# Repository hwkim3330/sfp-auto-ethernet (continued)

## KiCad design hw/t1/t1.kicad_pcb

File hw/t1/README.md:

# T1 SFP: 100/1000BASE-T1

Schematic, PCB (4 layers, routed), fab outputs and firmware are all in place.
**Order files are in [`jlc/`](jlc/), and the order sheet is [ORDER.md](ORDER.md).** The only open choice is **which PHY to use** (TG720 stock problem).

| Top | Bottom |
|---|---|
|  |  |

## Status

| | Result | How it was checked |
|---|---|---|
| Schematic | **ERC 0 errors, 0 warnings** ([erc.rpt](erc.rpt)) | eeschema's own ERC (`run_erc.sh`) |
| Schematic ↔ netlist | 175 pins, 0 mismatches | Netlist exported with `kicad-cli sch export netlist`, compared against the netlist in `make_t1.py` |
| Placement | 65 parts, no overlaps; housing height limits met | `make_t1.py` |
| Routing | **DRC 0 violations, 0 unconnected** ([drc.rpt](drc.rpt)) | Freerouting 1.9.0, then KiCad DRC |
| KiCad 9 | **DRC 0 errors, schematic parity clean, ERC 0 errors** ([kicad9-drc.rpt](kicad9-drc.rpt), [kicad9-erc.rpt](kicad9-erc.rpt)) | `sh ../check_kicad9.sh t1`: the official KiCad 9 image, as a reviewer would open it. Only warnings are "differs from the library copy" (KiCad 9's libraries hold newer revisions of the same parts) |
| Fab | Gerbers + drill ([fab/t1-gerbers.zip](fab/t1-gerbers.zip)), [BOM](fab/t1-bom.csv), [CPL](fab/t1-cpl.csv) | `export_t1.py` |
| Firmware | Builds: 1.7 KB flash / 280 B RAM, 0 warnings ([../../fw](../../fw)) | `make` |

## Circuit (every block is from its datasheet)

- **PHY:** DP83TG720S-Q1 (1000BASE-T1).
  - The **DP83TC812S-Q1 (100BASE-T1) fits the same footprint**. For the 100 Mb loadout, leave **FB3** unfitted (the 1.0 V buck → pins 9/21 ferrite); the TC812 regulates pin 21 itself.
  - The straps are all left at their defaults: SGMII, PHY address 0, autonomous, slave. The MCU must still set the SGMII polarity bits at start-up (see below).
- **SGMII:** SFP TD/RD → 100 nF AC coupling inside the module (as the MSA requires) → PHY TX_P/M (32/33) and RX_P/M (24/23).
- **MDI (Figure 8-1 / Table 8-1):** TRD → 100 nF DC-block → DLW32MH101XT2 CMC → H-MTD. CM termination is 2 × 1 kΩ to a node, then 4.7 nF + 100 kΩ from the node to GND. ESD is optional and left unfitted.
- **Power (Figure 8-3 / Table 8-2):**
  - The host's 3.3 V enters through the MSA's ferrites and a **TPS22918 load switch** (soft start ≈3.6 ms).
  - VDDA, VDDIO and VDD1P0 each get their own ferrite island.
  - Every power pin gets 10 nF + 100 nF; some also get 2.2 µF.
  - The decaps sit on the **bottom side**, in a ring under the PHY.
  - 1.0 V comes from a **TPS62822 buck**: 470 nH, 66.5 k / 100 k divider, 120 pF Cff.
  - Estimated module power **~0.7 W**, inside the SFP's 1.0 W power-up limit.
- **MCU:** STM32G031. It answers the host's I²C as the EEPROM (0x50) and the PHY bridge (0x56), and handles MDIO, TX_DISABLE and RX_LOS. See [`../../fw/`](../../fw/).

## Board

- 64.5 × 11.8 mm (the H-MTD overhangs a further 3.5 mm). The tab is 9.2 mm wide.
- Edge connector is the INF-8074i pattern (`../fp/sfp.pretty/SFP_Module_Edge`).
- 4 layers, **F / GND / GND / B** (JLC04101H-3313, 1.0 mm):

  | Layer | Use |
  |---|---|
  | F | pairs + signals + GND pour |
  | In1 | GND (solid) |
  | In2 | GND pour; slow signals (MDIO, LEDs, straps) may cross it, **except** under the bottom-side RX pair (`IN2_KEEPOUTS`), so every pair on B has an unbroken GND under it |
  | B | pairs + signals + GND pour |

- No pour among the edge fingers. A 0.6 mm no-copper strip runs along every edge (the panel's mouse-bite holes).
- The PHY's exposed pad gets 3 × 3 thermal vias to the planes.

## Changes after the design review (2026-09-30)

- **Every pair is laid by hand, coupled**, in `make_t1.py` (`_pair`): 0.114 mm lines, 0.152 mm gap (≈100 Ω differential on 3313), both lines on one layer with the same vias. The router only does the slow nets. From [lengths.txt](lengths.txt):

  | Pair | Layers | Vias P/N | Skew |
  |---|---|---|---|
  | SG_TX (SFP TD → PHY) | F | 0/0 | 0.44 mm |
  | SG_RX (PHY → SFP RD) | F | 0/0 | 0.00 mm |
  | TRD (PHY → DC block) | F | 0/0 | 0.44 mm |
  | DCB (DC block → CMC) | F | 0/0 | 0.08 mm |
  | MDI (CMC → H-MTD) | F | 0/0 | 2.25 mm |

  0.44 mm is about 3 ps, against an 800 ps SGMII UI.
- **SGMII polarity: both lanes run straight, P to P** (since the SFP edge fix of 2026-10; before it the edge was mirrored and the firmware inverted both lanes in SGMII_CTRL_1 bits 7/8). The firmware now leaves those bits at their reset 0. **Not verified on hardware.**
- **3.3 V inrush: TPS22918 load switch (U4).** The host's filtered 3.3 V → FB1/FB2 → VIN_RAW (1 µF) → U4 → +3V3 (10 µF). CT = 2.2 nF gives a ≈3.6 ms rise, so the 10 µF and the decaps load softly and the MSA's hot-plug limit holds by design. **Measure it on the first board.**
- **Two BOMs**: `jlc/bom-tg720.csv` + `cpl-tg720.csv` (1000BASE-T1) and `jlc/bom-tc812.csv` + `cpl-tc812.csv` (100BASE-T1: U1 = C3225813, FB3 left off).
- **H-MTD 1:1 print**: [fab/t1-1to1.pdf](fab/t1-1to1.pdf) (F.Cu + outline at 100 %). Print it without scaling and set the real connector on it before ordering.
- **Gold fingers are ENIG**, not the MSA's hard gold (≥ 0.38 µm). JLC offers no hard gold. Fine for tens of insertions on a bench; for a module that gets plugged often, order from a fab that plates hard gold (e.g. PCBWay).

## Earlier changes for ordering (2026-09-29)

- **H-MTD J2 = Rosenberger E6S20A-40MT5-Z**, drawn from the layout drawing MB_633.
  - Ground holes Ø1.74 / pad 2.5, **7.0 × 7.5** apart. The research said 9.3, but that is the outer width of the hatched areas; I measured the drawing myself.
  - Signal holes Ø0.7, 2.0 apart, 1.87 behind the front row.
  - The hatched solder areas are GND pads, and the no-routing keep-outs are rule areas.
  - Overhangs the board edge by 3.5 mm. The body sits entirely outside the cage, so the board is 64.5 mm long.
  - LCSC has no stock: hand-solder it.
- **U1 pins 12/13 cross over on purpose.** They leave the package M-over-P and the CMC takes P-over-M. The DP83TG720 corrects MDI polarity itself, and that can't be disabled (datasheet 6.4.7.2), so pin 12 drives the line's M side.
- **Buck is the TPS62822** (the TPS62821 is out of stock at LCSC; same package, pins and divider).
- **Panel (`panel_t1.py`):**
  - 5 boards, mouse-bites, **rails on 3 sides only** so the gold-finger edge stays straight (`../panel_rails.py`).
  - KiKit 1.6.0 is the version that works with KiCad 7; its `fab jlcpcb` can't drive this plotter, so the gerbers, BOM and CPL are written by our own code.

## Regenerating

```bash
python3 make_t1.py            # symbols, footprints, schematic, placed PCB (with nets)
sh run_erc.sh                 # eeschema ERC -> erc.rpt (headless, Xvfb)
python3 make_t1.py --route    # + planes, Freerouting, SES in, pours, DRC -> drc.rpt
python3 make_t1.py --reuse-ses  # reuse t1.ses (Freerouting results vary from run to run)
python3 export_t1.py          # single-board gerbers, BOM, CPL, previews, 1:1 PDF -> fab/
sh ../check_kicad9.sh t1      # the same board in KiCad 9: DRC + schematic parity + ERC
python3 panel_t1.py 5         # 5-board panel + JLC order files -> jlc/ (KiKit 1.6.0)
```

- The router is **Freerouting 1.9.0**, at `~/.local/share/freerouting/freerouting-1.9.0.jar`.
  - 2.x ignores the pass limit on the command line and never finishes on this board.
  - 1.9.0 needs a display, so it gets Xvfb `:98`.
- Freerouting's result changes on every run. **`t1.ses` in this repo is the run that came out DRC-clean.**
- Where the router kept failing, the design file lays copper before it runs, all locked:
  - `PREROUTES` / `PREVIAS`, hand-drawn:
    - every high-speed pair (above);
    - EN→VIN of the buck, routed under U3 because the no-connect PG pin blocks the direct way;
    - escape vias for U1's MDC/INT/RST, which share one lane past the crystal;
    - spokes from the pin 11/21 decap row to U1's bottom EP pad;
    - a shared ground via for C10/C16 and one for R4;
    - where the 0.6 mm edge strip closed the router's way: U4's ON pin, MDC, VDD1P0 pin 21, the MCU's ground, XO.
  - A ground via beside every capacitor ("dogbone"), except where `NO_DOGBONE` says it blocks a lane: the crystal's load caps and C21.
- After routing, `sfpgen` repairs what is left, keeping each change only if DRC is no worse:
  - removes escape vias the router didn't use;
  - joins open signal links (straight, via bridge, or a T into an existing track), before stitching so those links get the space first;
  - lays the GND stitching grid, 1 mm off the long edges where the panel's mouse bites are;
  - vias into ground islands.
- The panel's mouse-bite holes sit 0.1 mm into the board (was 0.25): at 0.25 they came within 0.16 mm of an In2 trace.
- KiCad 7 quirks, recorded in the code:
  - Standalone `LoadBoard` does not read `.kicad_pro`, so the rules are set in memory (`apply_rules`).
  - A footprint must be added to the board before `Flip`, or it segfaults.
  - A pad's `SetPos0` is required, or every pad collapses to the footprint origin.

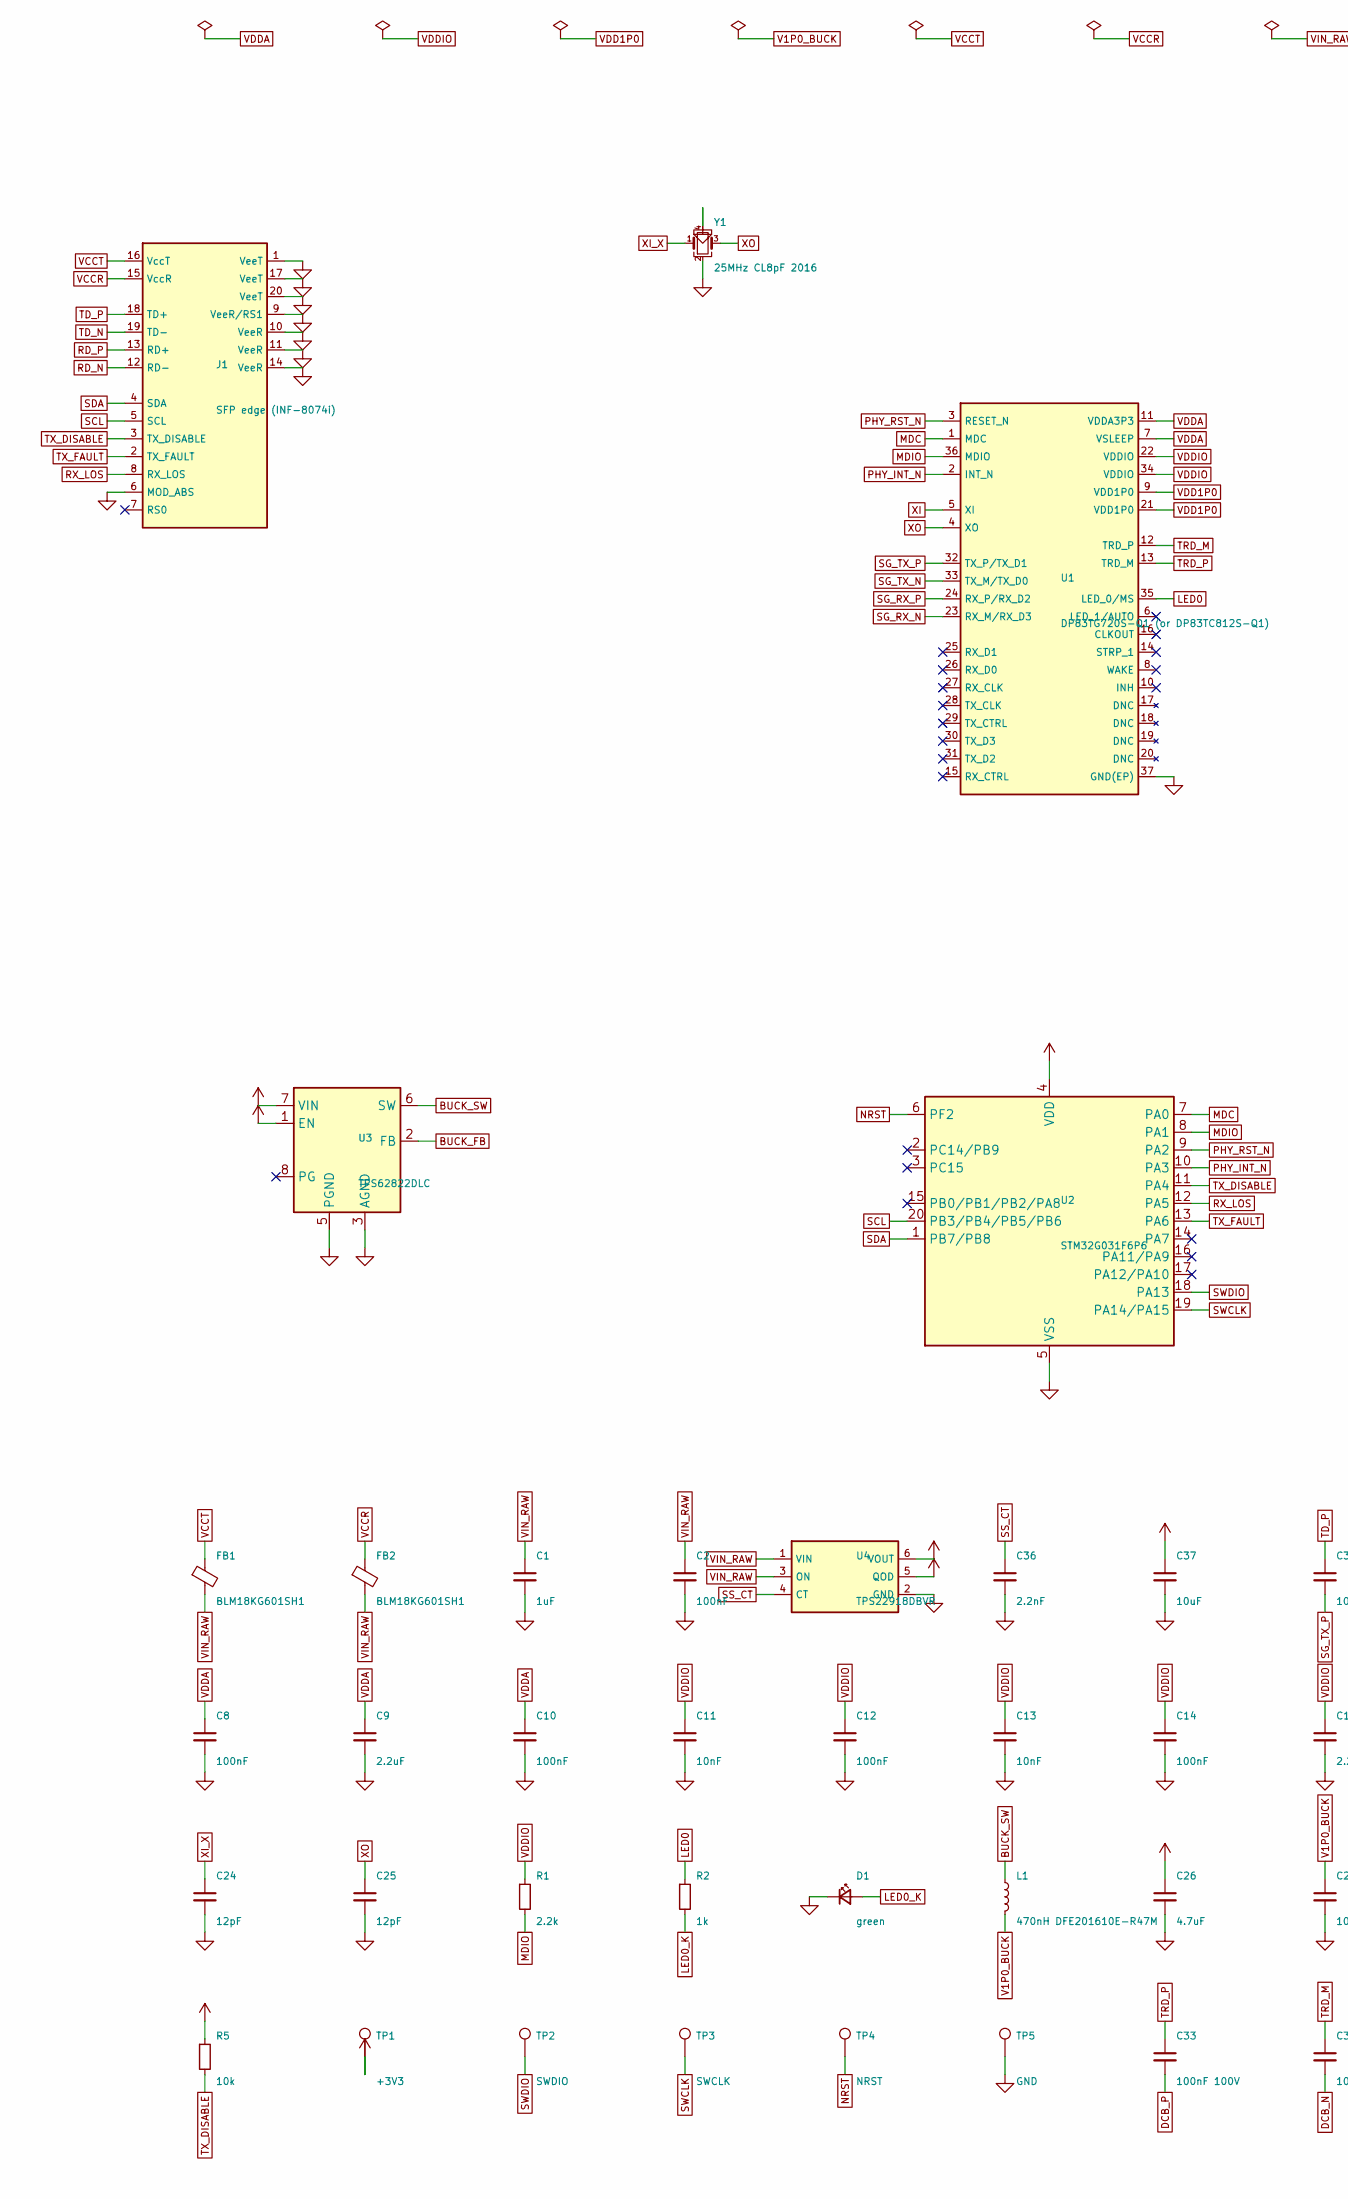
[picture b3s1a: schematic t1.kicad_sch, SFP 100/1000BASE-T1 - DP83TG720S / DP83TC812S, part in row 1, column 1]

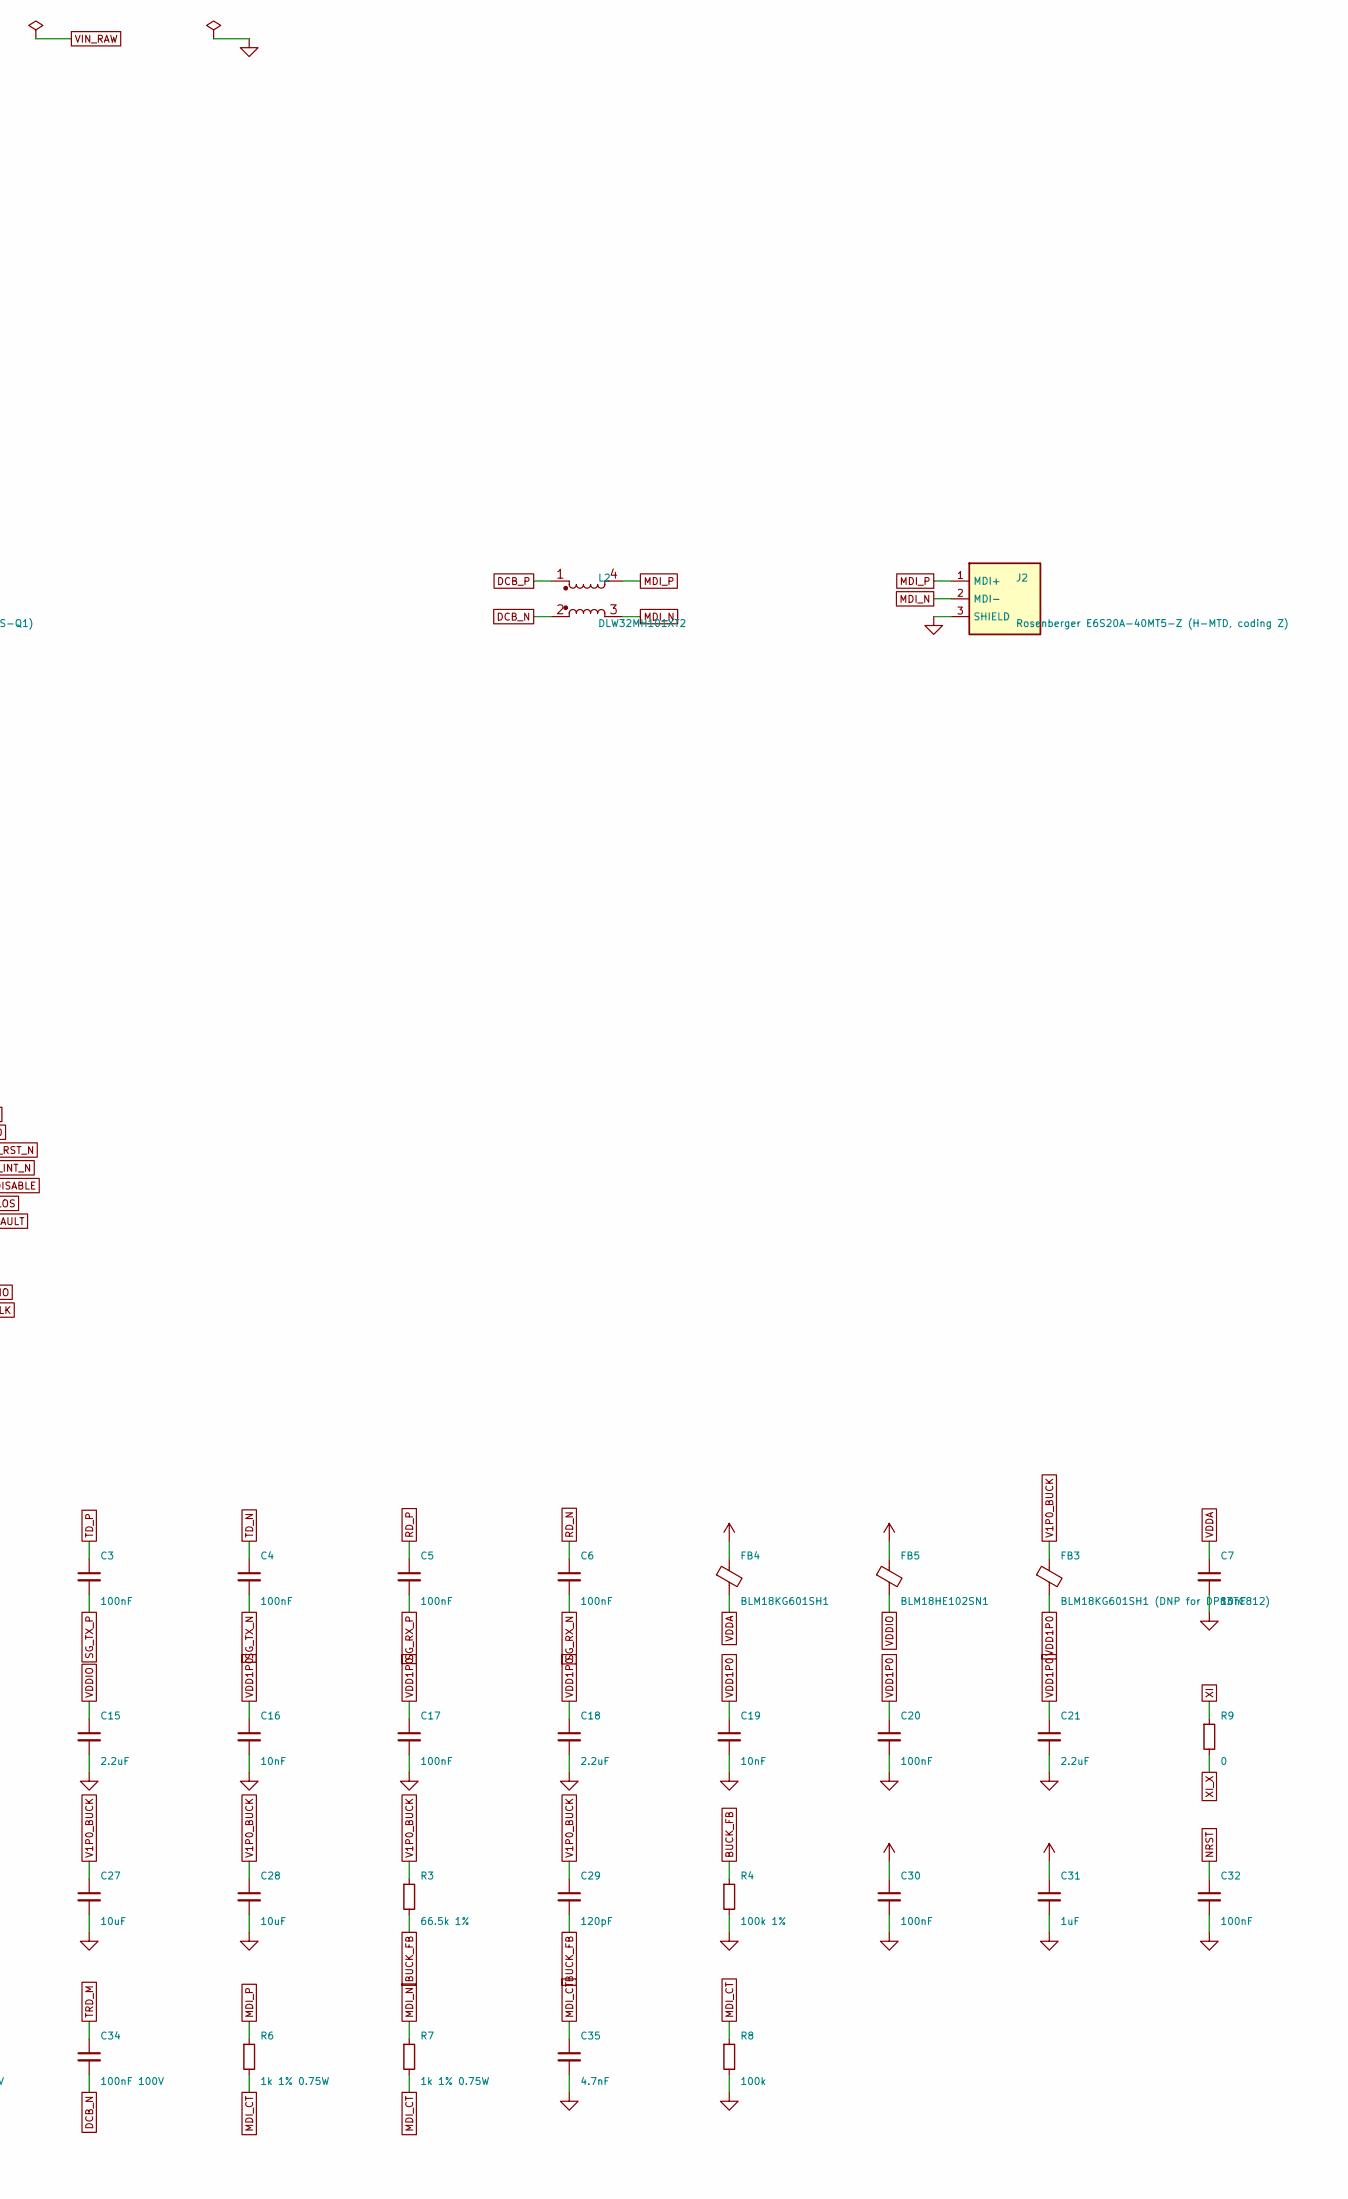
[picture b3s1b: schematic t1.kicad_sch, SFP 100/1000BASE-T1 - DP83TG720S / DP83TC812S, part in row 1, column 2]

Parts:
C1, C31: 1uF; C_0402_1005Metric; LCSC C52923
C2, C30, C32: 100nF; C_0402_1005Metric; LCSC C1525
C3, C4, C5, C6, C8, C10, C12, C14, C17, C20: 100nF; C_0201_0603Metric; LCSC C76928
C7, C11, C13, C16, C19: 10nF; C_0201_0603Metric; LCSC C285010
C9, C15, C18, C21: 2.2uF; C_0402_1005Metric; LCSC C12530
C24, C25: 12pF; C_0201_0603Metric; LCSC C50391
C26: 4.7uF; C_0402_1005Metric; LCSC C23733
C27, C28, C37: 10uF; C_0603_1608Metric; LCSC C19702
C29: 120pF; C_0201_0603Metric; LCSC C161406
C33, C34: 100nF 100V; C_0402_1005Metric; MPN GRM155R62A104KE14D; LCSC C162178
C35: 4.7nF; C_0402_1005Metric; LCSC C1538
C36: 2.2nF; C_0402_1005Metric; LCSC C106861
D1: green; LED_0402_1005Metric; LCSC C965793
FB1, FB2, FB4: BLM18KG601SH1; L_0603_1608Metric; MPN BLM18KG601SH1; LCSC C710379
FB3: BLM18KG601SH1 (DNP for DP83TC812); L_0603_1608Metric; MPN BLM18KG601SH1; LCSC C710379
FB5: BLM18HE102SN1; L_0603_1608Metric; MPN BLM18HE102SN1; LCSC C85828
J1: SFP edge (INF-8074i); SFP_Module_Edge
J2: Rosenberger E6S20A-40MT5-Z (H-MTD, coding Z); Rosenberger_HMTD_E6S20A_1P_RA; MPN E6S20A-40MT5-Z
L1: 470nH DFE201610E-R47M; L_Murata_DFE201610P; MPN DFE201610E-R47M; LCSC C269773
L2: DLW32MH101XT2; L_CommonMode_3225; MPN DLW32MH101XT2; LCSC C2935101
R1: 2.2k; R_0201_0603Metric; LCSC C142018
R2: 1k; R_0402_1005Metric; LCSC C11702
R3: 66.5k 1%; R_0201_0603Metric; LCSC C62193
R4: 100k 1%; R_0201_0603Metric; LCSC C106224
R5: 10k; R_0402_1005Metric; LCSC C25744
R6, R7: 1k 1% 0.75W; R_2010_5025Metric; MPN RC2010FK-071KL; LCSC C723477
R8: 100k; R_0402_1005Metric; LCSC C25741
R9: 0; R_0201_0603Metric; LCSC C106227
TP1: +3V3; TestPoint_Pad_D1.0mm
TP2: SWDIO; TestPoint_Pad_D1.0mm
TP3: SWCLK; TestPoint_Pad_D1.0mm
TP4: NRST; TestPoint_Pad_D1.0mm
TP5: GND; TestPoint_Pad_D1.0mm
U1: DP83TG720S-Q1 (or DP83TC812S-Q1); QFN-36-1EP_6x6mm_P0.5mm_EP3.7x3.7mm_ThermalVias; MPN DP83TG720SWRHARQ1; LCSC C2921292
U2: STM32G031F6P6; TSSOP-20_4.4x6.5mm_P0.65mm; MPN STM32G031F6P6; LCSC C529333
U3: TPS62822DLC; Texas_VSON-HR-8_1.5x2mm_P0.5mm; MPN TPS62822DLCR; LCSC C473385
U4: TPS22918DBVR; SOT-23-6; MPN TPS22918DBVR; LCSC C131941
Y1: 25MHz CL8pF 2016; Crystal_SMD_2016-4Pin_2.0x1.6mm; LCSC C7301943

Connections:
+3V3: C26.1, C30.1, C31.1, C37.1, FB4.1, FB5.1, R5.1, TP1.1, U2.4 (VDD), U3.1 (EN), U3.7 (VIN), U4.5 (QOD), U4.6 (VOUT)
BUCK_FB: C29.2, R3.2, R4.1, U3.2 (FB)
BUCK_SW: L1.1, U3.6 (SW)
DCB_N: C34.2, L2.2
DCB_P: C33.2, L2.1
GND: C1.2, C2.2, C7.2, C8.2, C9.2, C10.2, C11.2, C12.2, C13.2, C14.2, C15.2, C16.2, C17.2, C18.2, C19.2, C20.2, C21.2, C24.2, C25.2, C26.2, C27.2, C28.2, C30.2, C31.2, C32.2, C35.2, C36.2, C37.2, D1.1 (K), J1.1 (VeeT), J1.6 (MOD_ABS), J1.9 (VeeR/RS1), J1.10 (VeeR), J1.11 (VeeR), J1.14 (VeeR), J1.17 (VeeT), J1.20 (VeeT), J2.3 (SHIELD), R4.2, R8.2, TP5.1, U1.37 (GND(EP)), U2.5 (VSS), U3.3 (AGND), U3.5 (PGND), U4.2 (GND), Y1.2, Y1.4
LED0: R2.1, U1.35 (LED_0/MS)
LED0_K: D1.2 (A), R2.2
MDC: U1.1 (MDC), U2.7 (PA0)
MDIO: R1.2, U1.36 (MDIO), U2.8 (PA1)
MDI_CT: C35.1, R6.2, R7.2, R8.1
MDI_N: J2.2 (MDI-), L2.3, R7.1
MDI_P: J2.1 (MDI+), L2.4, R6.1
NRST: C32.1, TP4.1, U2.6 (PF2)
PHY_INT_N: U1.2 (INT_N), U2.10 (PA3)
PHY_RST_N: U1.3 (RESET_N), U2.9 (PA2)
RD_N: C6.1, J1.12 (RD-)
RD_P: C5.1, J1.13 (RD+)
RX_LOS: J1.8 (RX_LOS), U2.12 (PA5)
SCL: J1.5 (SCL), U2.20 (PB3/PB4/PB5/PB6)
SDA: J1.4 (SDA), U2.1 (PB7/PB8)
SG_RX_N: C6.2, U1.23 (RX_M/RX_D3)
SG_RX_P: C5.2, U1.24 (RX_P/RX_D2)
SG_TX_N: C4.2, U1.33 (TX_M/TX_D0)
SG_TX_P: C3.2, U1.32 (TX_P/TX_D1)
SS_CT: C36.1, U4.4 (CT)
SWCLK: TP3.1, U2.19 (PA14/PA15)
SWDIO: TP2.1, U2.18 (PA13)
TD_N: C4.1, J1.19 (TD-)
TD_P: C3.1, J1.18 (TD+)
TRD_M: C34.1, U1.12 (TRD_P)
TRD_P: C33.1, U1.13 (TRD_M)
TX_DISABLE: J1.3 (TX_DISABLE), R5.2, U2.11 (PA4)
TX_FAULT: J1.2 (TX_FAULT), U2.13 (PA6)
V1P0_BUCK: C27.1, C28.1, C29.1, FB3.1, L1.2, R3.1
VCCR: FB2.1, J1.15 (VccR)
VCCT: FB1.1, J1.16 (VccT)
VDD1P0: C16.1, C17.1, C18.1, C19.1, C20.1, C21.1, FB3.2, U1.9 (VDD1P0), U1.21 (VDD1P0)
VDDA: C7.1, C8.1, C9.1, C10.1, FB4.2, U1.7 (VSLEEP), U1.11 (VDDA3P3)
VDDIO: C11.1, C12.1, C13.1, C14.1, C15.1, FB5.2, R1.1, U1.22 (VDDIO), U1.34 (VDDIO)
VIN_RAW: C1.1, C2.1, FB1.2, FB2.2, U4.1 (VIN), U4.3 (ON)
XI: R9.1, U1.5 (XI)
XI_X: C24.1, R9.2, Y1.1
XO: C25.1, U1.4 (XO), Y1.3

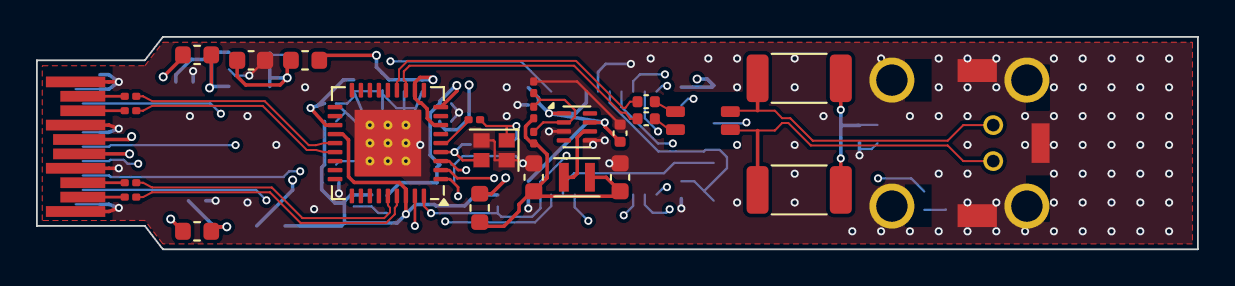
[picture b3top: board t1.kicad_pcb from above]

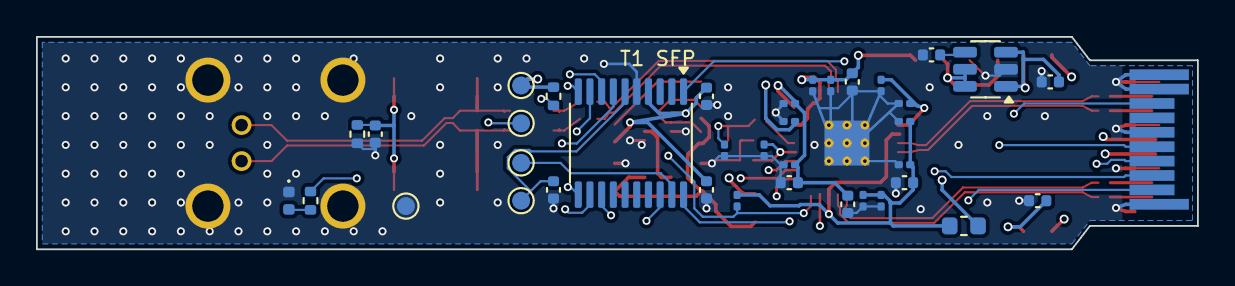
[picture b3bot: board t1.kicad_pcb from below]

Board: 4 copper layers, 64.5 x 11.8 mm, 64 parts (37 on the bottom side), 44 nets.

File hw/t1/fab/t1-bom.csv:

Comment,Designator,Footprint,MPN,Qty,Fitted
1uF,"C1,C31",C_0402_1005Metric,,2,yes
100nF,"C2,C30,C32",C_0402_1005Metric,,3,yes
12pF,"C24,C25",C_0201_0603Metric,,2,yes
4.7uF,C26,C_0402_1005Metric,,1,yes
120pF,C29,C_0201_0603Metric,,1,yes
100nF,"C3,C4,C5,C6,C8,C10,C12,C14,C17,C20",C_0201_0603Metric,,10,yes
100nF 100V,"C33,C34",C_0402_1005Metric,GRM155R62A104KE14D,2,yes
4.7nF,C35,C_0402_1005Metric,,1,yes
2.2nF,C36,C_0402_1005Metric,,1,yes
10uF,"C37,C27,C28",C_0603_1608Metric,,3,yes
10nF,"C7,C11,C13,C16,C19",C_0201_0603Metric,,5,yes
2.2uF,"C9,C15,C18,C21",C_0402_1005Metric,,4,yes
green,D1,LED_0402_1005Metric,,1,yes
BLM18KG601SH1,"FB1,FB2,FB4",L_0603_1608Metric,BLM18KG601SH1,3,yes
BLM18KG601SH1 (DNP for DP83TC812),FB3,L_0603_1608Metric,BLM18KG601SH1,1,yes
BLM18HE102SN1,FB5,L_0603_1608Metric,BLM18HE102SN1,1,yes
"Rosenberger E6S20A-40MT5-Z (H-MTD, coding Z)",J2,Rosenberger_HMTD_E6S20A_1P_RA,E6S20A-40MT5-Z,1,yes
470nH DFE201610E-R47M,L1,L_Murata_DFE201610P,DFE201610E-R47M,1,yes
DLW32MH101XT2,L2,L_CommonMode_3225,DLW32MH101XT2,1,yes
2.2k,R1,R_0201_0603Metric,,1,yes
1k,R2,R_0402_1005Metric,,1,yes
66.5k 1%,R3,R_0201_0603Metric,,1,yes
100k 1%,R4,R_0201_0603Metric,,1,yes
10k,R5,R_0402_1005Metric,,1,yes
1k 1% 0.75W,"R6,R7",R_2010_5025Metric,RC2010FK-071KL,2,yes
100k,R8,R_0402_1005Metric,,1,yes
0,R9,R_0201_0603Metric,,1,yes
DP83TG720S-Q1 (or DP83TC812S-Q1),U1,QFN-36-1EP_6x6mm_P0.5mm_EP3.7x3.7mm_ThermalVias,DP83TG720SWRHARQ1,1,yes
STM32G031F6P6,U2,TSSOP-20_4.4x6.5mm_P0.65mm,STM32G031F6P6,1,yes
TPS62822DLC,U3,Texas_VSON-HR-8_1.5x2mm_P0.5mm,TPS62822DLCR,1,yes
TPS22918DBVR,U4,SOT-23-6,TPS22918DBVR,1,yes
25MHz CL8pF 2016,Y1,Crystal_SMD_2016-4Pin_2.0x1.6mm,,1,yes

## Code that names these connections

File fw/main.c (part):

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 * transaction runs, so there is no interrupt and no shared state to guard.
 *
 * Pins (TSSOP-20, see hw/t1/make_t1.py MCU map):
 *   PB7 SDA   PB6 SCL   (AF6, open drain)
 *   PA0 MDC   PA1 MDIO  (bit-banged; MDIO open drain, 2.2k to VDDIO on the board)
 *   (RJ45: PA0 MDIO, PA1 MDC, PA4 TX_FAULT, PA5 TX_DISABLE, PA6 RX_LOS)
 *   PA2 PHY_RST_N out   PA3 PHY_INT_N in
 *   PA4 TX_DISABLE in (pulled up on the board: high/open = disabled)
 *   PA5 RX_LOS out, open drain (high = no link)
 *   PA6 TX_FAULT out, open drain, held low (no fault)
 *   (T1S: PB8 SCL, PA10 SDA (pin 17, PA12 remapped), PC15 RX_LOS,
 *    PA4 TX_FAULT, PA6 TX_DISABLE - see hw/t1s/make_t1s.py)
 *
 * Register references: DP83TG720S-Q1 SNLS604G - BMSR (0x01) bit 2 link;
 * REGCR 0x0D / ADDAR 0x0E indirect access; PMA_PMD_CONTROL MMD1 0x0834
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/* ------------------------------------------------------------------ GPIO */
#define PIN(n)   (1u << (n))
#if VARIANT_RJ45                /* hw/rj45/make_rj45.py MCU map: placed for its In2 bus's lane order */
#define MDC      1
#define MDIO     0
#define PHY_RST  2
#define PHY_INT  3
#define TX_DIS   5
#define RX_LOS   6
#define TX_FAULT 4
#else
#define MDC      0
#define MDIO     1
#define PHY_RST  2
#define PHY_INT  3
#define TX_DIS   4
#define RX_LOS   5
#define TX_FAULT 6
#endif
/* where TX_DISABLE, TX_FAULT and RX_LOS are. On T1S the MCU's pins follow
 * the SFP fingers' order along the board's two In2 buses: RX_LOS and SCL go
 * along the north edge (PC15, pin 3; PB8, pin 1), SDA, TX_DISABLE and
 * TX_FAULT along the south edge (PA10 on pin 17, PA6, PA4) */
#if VARIANT_T1S
#define TXDIS_PORT  GPIOA
#define TXDIS_PIN   6
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#define TXDIS_PORT  GPIOA
#define TXDIS_PIN   TX_DIS
#define TXF_PORT    GPIOA
#define TXF_PIN     TX_FAULT
#define RXLOS_PORT  GPIOA
#define RXLOS_PIN   RX_LOS
#endif
#define los_set() (RXLOS_PORT->BSRR = PIN(RXLOS_PIN))     /* released: loss of signal */
#define los_clr() (RXLOS_PORT->BRR = PIN(RXLOS_PIN))
#if VARIANT_T1S                /* hw/t1s/make_t1s.py MCU map */
#define FPGA_LINK 7            /* PA7 (pin 14) in: SGMII up, from the FPGA */
#define FPGA_DONE 11           /* PA11 (pin 16) in: configuration done (4.7k pull-up) */
#define FPGA_RECONF 0          /* PB0 (pin 15) out, open drain: low = reload (4.7k pull-up).
                                  PB1, PB2 and PA8 share the pin and stay analog */
#endif

static void gpio_mode(GPIO_TypeDef *g, int pin, uint32_t mode, int od, uint32_t pull)
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    pa_clr(PHY_RST);
    gpio_mode(GPIOA, PHY_RST, 1, 0, 0);          /* PHY held in reset first */
    pa_clr(MDC);
    gpio_mode(GPIOA, MDC, 1, 0, 0);
    pa_set(MDIO);
    gpio_mode(GPIOA, MDIO, 1, 1, 0);             /* open drain, board pull-up */
    gpio_mode(GPIOA, PHY_INT, 0, 0, 1);
    gpio_mode(TXDIS_PORT, TXDIS_PIN, 0, 0, 0);
    /* EXTI on both edges of TX_DISABLE (EXTICR: port A = 0, C = 2) */
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    TXF_PORT->BRR = PIN(TXF_PIN);
    gpio_mode(TXF_PORT, TXF_PIN, 1, 1, 0);       /* held low: no fault */
#if VARIANT_T1S
    gpio_mode(GPIOA, FPGA_LINK, 0, 0, 0);        /* in; R26 pulls it up (it is also the FPGA's SSPI_CS_N) */
    gpio_mode(GPIOA, FPGA_DONE, 0, 0, 0);
    GPIOB->BSRR = PIN(FPGA_RECONF);
    gpio_mode(GPIOB, FPGA_RECONF, 1, 1, 0);      /* released */
#endif
#if VARIANT_T1S
    /* PB8 SCL (pin 1, which PB7 shares: PB7 stays analog) and PA10 SDA (pin
     * 17, PA12's pad remapped to PA10), both AF6 I2C1, open drain */
    SYSCFG->CFGR1 |= SYSCFG_CFGR1_PA12_RMP;
    gpio_mode(GPIOB, 8, 2, 1, 0);
    GPIOB->AFR[1] = (GPIOB->AFR[1] & ~(0xFu << (4 * (8 - 8)))) | (6u << (4 * (8 - 8)));
    gpio_mode(GPIOA, 10, 2, 1, 0);
    GPIOA->AFR[1] = (GPIOA->AFR[1] & ~(0xFu << (4 * (10 - 8)))) | (6u << (4 * (10 - 8)));
#else
    for (int p = 6; p <= 7; p++) {               /* PB6 SCL, PB7 SDA: AF6, open drain */
        gpio_mode(GPIOB, p, 2, 1, 0);
        GPIOB->AFR[0] = (GPIOB->AFR[0] & ~(0xFu << (4 * p))) | (6u << (4 * p));
    }
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
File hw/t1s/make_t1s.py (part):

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part('C1', 'Device:C_Small', '1uF', C0402, {1: 'VIN_RAW', 2: 'GND'}, (7.3, 1.1), side='B')
part('C2', 'Device:C_Small', '100nF', C0402, {1: 'VIN_RAW', 2: 'GND'}, (9.2, 1.1), side='B')
part('U4', 'sfp:TPS22918', 'TPS22918DBVR', 'Package_TO_SOT_SMD:SOT-23-6',
     {1: 'VIN_RAW', 2: 'GND', 3: 'VIN_RAW', 4: 'SS_CT', 5: '+3V3', 6: '+3V3'}, U4_AT, side='B', rot=90,
     mpn='TPS22918DBVR')
part('C36', 'Device:C_Small', '2.2nF', C0402, C36_NETS, C36_AT)
part('C37', 'Device:C_Small', '10uF', C0402, {1: '+3V3', 2: 'GND'}, C37_AT, rot=180)
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
# 125 MHz LVDS reference, AC coupled at the FPGA
part('X1', 'sfp:OSC_LVDS', 'OB2EL89CLIB112YLC-125M', 'sfp:Oscillator_YXC_3225-6Pin_LVDS',
     {1: '+3V3', 2: None, 3: 'GND', 4: 'OSC_P', 5: 'OSC_N', 6: '+3V3'}, (23.0, 3.55), rot=90,
     mpn='OB2EL89CLIB112YLC-125M')
# the upper lane carries OUT+ to REFCLKM: the lanes would otherwise cross, and an
# inverted reference clock is still the same clock
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       32: 'GND', 33: 'GND'}
part('U5', 'sfp:LAN8670', 'LAN8670C2-E/LMX', 'Package_DFN_QFN:VQFN-32-1EP_5x5mm_P0.5mm_EP3.5x3.5mm', PHY, PHY_AT,
     mpn='LAN8670C2-E/LMX')
# pins 30/31 carry the pair swapped: TRXP (31) is the outer lane to the upper
# cap and TRXN (30) the inner to the lower, so the two never cross. 10BASE-T1S
# is DME coded, which does not care which way round the pair is
# straps (DS 3.5, no internal resistors): MII + crystal = MODE 01, PHY address 0
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part('R20', 'Device:R_Small', '10k', R0201, {1: '+3V3', 2: 'PHY_RST_N'}, (35.5, -0.75), side='B', rot=90)
part('R21', 'Device:R_Small', '12.4k 1%', R0402, {1: 'RBIAS', 2: 'GND'}, (28.1, 4.2), side='B', rot=90)
part('Y1', 'Device:Crystal_GND24_Small', '25MHz CL12pF 2016', 'Crystal:Crystal_SMD_2016-4Pin_2.0x1.6mm',
     {1: 'XTI', 2: 'GND', 3: 'XTO', 4: 'GND'}, (31.4, 4.0), side='B', rot=180)   # XTI east, XTO west, as pins 27 / 28
part('C30', 'Device:C_Small', '18pF', C0201, {1: 'XTO', 2: 'GND'}, (29.4, 4.0), side='B', rot=90)
part('C31', 'Device:C_Small', '18pF', C0201, {1: 'XTI', 2: 'GND'}, (33.5, 4.0), side='B', rot=90)
for i, (at, r) in enumerate((((29.7, 2.3), 180), ((32.45, 2.1), 180), ((30.2, -1.45), 0), ((35.5, 3.75), 90))):
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# ---------------------------------------------------------------- MCU
# the pin order follows the In2 buses (below), which follow the fingers'
# order (SFF-8419: RX_LOS +2.2, SCL -0.2, SDA -1.0, TX_DISABLE -1.8,
# TX_FAULT -2.6, underneath): RX_LOS and SCL go along the north edge to pins
# 3 / 1, SDA, TX_DISABLE and TX_FAULT along the south edge to the bottom row.
# I2C1 on PB8 (pin 1, SCL, AF6) and PA10 (pin 17 with the PA12->PA10 remap,
# SDA, AF6); RX_LOS on PC15, TX_FAULT PA4, TX_DISABLE PA6 (fw: VARIANT_T1S)
MCU = {1: 'SCL', 2: None, 3: 'RX_LOS', 4: '+3V3', 5: 'GND', 6: 'NRST', 7: 'MDC', 8: 'MDIO',
       9: 'PHY_RST_N', 10: 'PHY_INT_N', 11: 'TX_FAULT', 12: None, 13: 'TX_DISABLE',
       14: 'FPGA_LINK', 15: 'FPGA_RECONFIG_N', 16: 'FPGA_DONE', 17: 'SDA', 18: 'SWDIO', 19: 'SWCLK', 20: None}
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# MII, on top. TX: the FPGA's right column straight across to the PHY's left
# side, each line one pitch down on the way. RX: the bottom row down into
# seven lanes along the bottom edge, to the PHY's bottom pins and round its
# corner up to its right side; TXCLK above them to pin 12. The PHY pins the
# lanes pass (right side 18/21/22, bottom 10/11/13/14) take a via in the pad.
_MW = 0.1                       # 0.25 mm pitch lanes: 0.1 lines, 0.15 gaps
_px = lambda pin: [p for p in _PHY_PADS if p[0] == pin][0][1:]
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# the strap below it (R10/R11/R14/R15 next to the right side, R12 under CRS)
PREVIAS += [('RXD3', (34.0, 1.75), _DV), ('RXD2', (34.0, 1.25), _DV), ('RXDV', (34.0, -0.25), _DV),
            ('RXD1', (34.0, -0.75), _DV),
            # CRS, RXD0 (bottom side) and TXEN (left side): a via in the pad, as pins 10-14
            ('CRS', (32.25, -2.66), MIN_VIA), ('RXD0', (32.75, -2.66), MIN_VIA), ('TXEN', (28.34, -1.25), MIN_VIA)]
PREROUTES += [('RXD3', 'B', [(34.0, 1.75), (34.25, 2.0), (34.6, 2.28)], _BW),
              ('RXD2', 'B', [(34.0, 1.25), (34.6, 1.32)], _BW),
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              ('CRS', 'B', [(32.25, -2.66), (32.85, -3.25), (32.85, -3.43)], _BW),
              ('RXD0', 'B', [(32.75, -2.66), (33.3, -3.2), (35.2, -3.2), (35.5, -3.43)], _BW),
              ('TXEN', 'B', [(28.34, -1.25), (28.6, -1.5), (28.6, -2.08)], _BW)]
# XTI (pin 27): a via in the pad, then underneath between the crystal's pads 3 and 4
PREVIAS += [('XTI', (31.75, 2.75), MIN_VIA), ('XTO', (31.25, 2.66), MIN_VIA)]
PREROUTES += [('XTI', 'B', [(31.75, 2.75), (32.0, 3.0), (32.0, 3.1)], _BW),
              ('XTO', 'B', [(31.25, 2.66), (31.35, 2.8), (31.35, 4.0), (31.0, 4.3)], _BW)]
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# the long runs on In2 between those vias. Found once by a maze search over
# this board before its dogbones went in (8-way, 0.025 mm grid, 0.15 mm
# clearance), with each line held to its lane along the south edge so the
# lanes stack in the order the MCU's pins take them: V1P2, RECONFIG_N, DONE,
# SDA above the pins' via row, FPGA_LINK, TX_DISABLE and TX_FAULT below it.
# Along the north edge SCL and RX_LOS; VDDHAQ leaves the ball field through
# row C and runs under the MCU; MISO crosses over the flash. Since the SFP
# edge fix (2026-10) the west ends are laid by hand from the fingers' vias:
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
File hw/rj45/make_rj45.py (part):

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     {1: 'VIN_RAW', 2: 'GND', 3: 'VIN_RAW', 4: 'SS_CT', 5: '+3V3', 6: '+3V3'}, (13.0, -4.15), mpn='TPS22918DBVR')
# below the HSI pair: above it the RD pair leaves 3.2 mm to the edge, the
# package's courtyard is 3.4. Its soft-start and output caps underneath.
part('C44', 'Device:C_Small', '2.2nF', C0402, {1: 'SS_CT', 2: 'GND'}, (15.6, -4.9))   # beside U4's pin 4, out of the edge strip
part('C45', 'Device:C_Small', '10uF', C0603, {1: '+3V3', 2: 'GND'}, (15.7, -4.6), side='B')

# SerDes: host -> module (TD, fingers 18/19, below the centreline) coupled at
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# side that U1's power pins need; the front has the buck.) Its nine slow lines
# run the length of the board: under the magnetics on In2 / bottom, then
# through the gaps of the jack's pin field.
# GPIOs placed for the slow bus's lane order (fw/main.c VARIANT_RJ45): MDIO PA0,
# MDC PA1, TX_FAULT PA4, TX_DISABLE PA5, RX_LOS PA6
MCU = {1: 'SDA', 2: None, 3: None, 4: '+3V3', 5: 'GND', 6: 'NRST', 7: 'MDIO', 8: 'MDC',
       9: 'PHY_RST_N', 10: 'PHY_INT_N', 11: 'TX_FAULT', 12: 'TX_DISABLE', 13: 'RX_LOS',
       14: None, 15: None, 16: None, 17: None, 18: 'SWDIO', 19: 'SWCLK', 20: 'SCL'}
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
PREROUTES = [_stub(pin, net, xy, r) for ref, pin, net, xy, r in DECAP]
PREVIAS = []
PREROUTES += [_stub(8, 'AVDD33', (19.9, 4.75), 270),            # pin 8 shares C9 with pin 7
              _stub(38, 'HSO_P', (15.0, -1.8), 0, 0.48, 0.157),
              _stub(37, 'HSO_N', (15.0, -2.75), 0, 0.48, 0.157)]
# right side fan (bottom): pin -> 0.6 out -> the fan's end; power pins on to a
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PREROUTES.append(('BOB', 'B', [(31.46, 4.5), (31.46, 5.1), (41.6, 5.1), (42.125, 4.575), (42.125, 4.4)], 0.2))
PREROUTES += [('BOB', 'B', [(x, 4.5), (x, 5.1)], 0.2) for x in (34.46, 37.46, 40.46)]

# RSET: out of pin 12, right under C10's pad, into R9; R9's ground to a via
PREROUTES += [('RSET', 'B', [u1_pin(12), (21.7, 3.45), (22.15, 3.45), (22.53, 3.95)])]
# (R9's ground end takes the pour of its own side: with U1 on top a via here
# sat in the In2 lanes' way)
# XI: straight up from pin 10 between C9 and C10, a via, then on top to X1 pin 3
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PREVIAS += [('GND', (36.8, 3.0))]       # return via beside the layer change (east of it the CMT3 via leaves no room)

PREVIAS += [('XI', XI_VIA)]
# U1's RST/MDC/MDIO (pins 1/2/3, top-left corner): each to an escape via,
# the router takes them on through In2 to the MCU. MDC and MDIO step left on
# parallel diagonals so MDIO can climb between MDC and C7; RST leaves left.
PREROUTES += [('PHY_RST_N', 'B', [u1_pin(1), (17.3, 3.15), (16.45, 3.15), (16.2, 3.4), (16.2, 3.45)]),
              ('MDC', 'B', [u1_pin(2), (17.7, 3.4), (17.35, 3.75), (17.3, 3.8), (17.3, 4.25)], 0.127),
              ('MDIO', 'B', [u1_pin(3), (18.1, 3.42), (17.75, 3.77), (17.75, 4.6), (17.7, 4.65), (17.7, 5.05)], 0.127)]
PREVIAS += [('PHY_RST_N', (16.2, 3.45)), ('MDC', (17.3, 4.25)), ('MDIO', (17.7, 5.05))]
# CFG1/CFG0 (pins 30/29, bottom edge): both down through the 0.78 mm between
# C16 and C15, then along under them to their straps
PREROUTES += [('CFG1', 'B', [u1_pin(30), (19.726, -3.3), (19.726, -4.9), (19.576, -5.05), (18.7, -5.05), (18.52, -5.15)]),
              ('CFG0', 'B', [u1_pin(29), (20.074, -3.3), (20.074, -4.9), (20.224, -5.05), (21.4, -5.05), (21.58, -5.12)])]
# U1's thermal vias, our own 3 x 3 at 1.2 mm: the library's _ThermalVias
# version puts a 4.3 mm copper pad and a +-1.9 mm grid on the far side (top),
# where the top side's routing wants to pass. 3 x 3 inside the EP is enough for ~0.45 W.
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
_UX = {n: 59.2 - 2.925 + 0.65 * k for k, n in enumerate(range(10, 0, -1))}   # bottom row, pin 10 at the left
_UXT = {n: 59.2 - 2.925 + 0.65 * k for k, n in enumerate(range(11, 21))}     # top row, pin 11 at the left
# top: TX_DISABLE, RX_LOS, TX_FAULT (pins 11/12/13), lanes 2.6/2.9/3.2 under the peg
for net, pin, yb, xb, ya, x1, lane in (('TX_FAULT', 11, 2.87, 48.32, 4.14, 50.66, 2.6),
                                       ('TX_DISABLE', 12, 3.175, 48.215, 4.44, 50.77, 2.9),
                                       ('RX_LOS', 13, 3.48, 48.11, 4.74, 50.88, 3.2)):
    vx, vy = _mcu_via(net, _UXT[pin], True)
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    PREROUTES.append((net, 'In2', [(42.5, yb), (xb, yb), (xb + 1.27, ya), (vx, ya), (vx, vy)], _BW))
PREROUTES.append(('+3V3', 'In2', [(42.5, -2.21), (42.0, -2.65)], _BW))
PREVIAS.append(('+3V3', (42.0, -2.65), MIN_VIA))   # into the In3 plane
# bottom: PHY_INT_N, PHY_RST_N, MDIO (pins 10/9/8)
for net, pin, yb, xb, ya in (('PHY_INT_N', 10, -4.14, 48.12, -2.87), ('PHY_RST_N', 9, -4.44, 48.23, -3.175),
                             ('MDC', 8, -4.74, 48.34, -3.48)):
    vx, vy = _mcu_via(net, _UX[pin], False)
    PREROUTES.append((net, 'In2', [(43.5, yb), (xb, yb), (xb + 1.27, ya), (vx, ya), (vx, vy)], _BW))
# MDC underneath: under pin 2, between 2 and 1, round 1's right side to a via,
# then In2 in a fourth lane under MDIO's
vx, vy = _mcu_via('MDIO', _UX[7], False)
PREROUTES += [('MDIO', 'B', [(42.8, -5.08), (43.28, -4.6), (43.4, -4.6), (44.0, -4.6), (48.0, -4.6), (49.425, -3.175), (51.0, -3.175), (51.6, -3.775), (51.6, -4.4)], _BW),
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
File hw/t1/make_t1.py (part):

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
# ---------------------------------------------------------------- PHY
PHY = {1: 'MDC', 2: 'PHY_INT_N', 3: 'PHY_RST_N', 4: 'XO', 5: 'XI', 6: None,
       # 12/13 cross over on purpose: pin 12 (TRD_P) drives the line's M side. They
       # leave the package M-over-P and the CMC takes P-over-M; the PHY corrects
       # MDI polarity itself and that cannot be turned off (datasheet 6.4.7.2)
       7: 'VDDA', 8: None, 9: 'VDD1P0', 10: None, 11: 'VDDA', 12: 'TRD_M', 13: 'TRD_P',
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    ('21', 'VDD1P0', ('10nF', '100nF', '2.2uF')),
]
# decaps sit on the BOTTOM, in a ring under the PHY (U1 at 19.5, 0, turned
# 180 so its SGMII pins face the fingers and MDC/INT/RST face the MCU)
_slots = [  # (x, y, rot) in DECAP order
    (21.4, 3.2, 90), (20.4, 3.2, 90), (19.2, 3.4, 90),      # pin 11 VDDA
    (22.7, 1.2, 0),                                          # pin 7 VSLEEP
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
# 25 MHz crystal, CL 8 pF -> 2 x 12 pF (less ~2 pF of strays each)
part('Y1', 'Device:Crystal_GND24_Small', '25MHz CL8pF 2016', 'Crystal:Crystal_SMD_2016-4Pin_2.0x1.6mm',
     {1: 'XI_X', 2: 'GND', 3: 'XO', 4: 'GND'}, (25.4, -0.4), rot=180)   # 180: XI/XO face U1's pins 5/4 uncrossed
# XI series resistor: the DP83TC812 wants 100 ohm in series with XI when it
# runs from a crystal (SNLS654D Table 5-1, pin 5); the DP83TG720 asks for none,
# so its loadout fits 0 ohm here
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# the pair's tail to a via for its decaps underneath
PREROUTES += [('VDDIO', 'F', [(20.5, -2.838), (20.5, -3.95)])]
PREVIAS += [('VDDIO', (20.5, -3.95))]   # C21 underneath moved west for it; 35/36 still go down past it
# LED0 (pin 35) likewise, to a via below VDDIO's
PREROUTES += [('LED0', 'F', [(21.0, -2.838), (21.0, -4.6)])]
PREVIAS += [('LED0', (21.0, -4.6))]
# the bottom-row decaps' ground (C11/C12/C21) sits in a pour pocket under U1
# with no via: one between U1's west corner and the TX pair, which runs at
# -4.3 so the via fits between them on top
PREVIAS += [('GND', (15.4, -3.67))]
# MDC (U1 pin 1) straight to a via for the MCU underneath
PREROUTES += [('MDC', 'F', [(22.338, -2.0), (22.95, -2.0), (23.4, -2.45), (23.4, -2.95)])]
PREVIAS += [('MDC', (23.4, -2.95))]
# VDD1P0 at U1 pin 21: left of the decap column underneath, then to C19
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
